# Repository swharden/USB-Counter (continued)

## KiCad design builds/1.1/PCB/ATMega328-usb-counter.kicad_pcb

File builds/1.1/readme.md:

# USB Frequency Counter (rev 1.1)

* I ordered this PCB on 2019-07-28
* I built this device on 2019-08-03

### PCB Design

### Schematic

## Changes from rev 1.0
* improved RF amplifier design
* alternate path to bypass RF amplifier
* corrected counter pin connections
* free a MCU pin by making the status LED the gate
* add a header for the serial LED display
* run MCU at 14.7456 MHz
  * allows much faster serial transmission
  * no longer accepts external 10MHz reference
  * may still accept external gate
* added screw holes
  * they're floating (not grounded) - should they be grounded?
* switched to micro USB (from mini USB)

## Components
* all passives are 0805 (~$1)
* [SBAV99WT1G SC-70 dual diode](https://www.mouser.com/ProductDetail/ON-Semiconductor/SBAV99WT1G?qs=%2Fha2pyFaduhs9dhfVWP8oT%252BsAj5t0ZSYddkb6PuTtd0%3D) 215 mA ($0.29)
* [14.7456MHz TCXO](https://www.mouser.com/ProductDetail/Fox/FOX924B-147456?qs=sGAEpiMZZMt8oz%2FHeiymADfzZKRiEXclvcmWd5jLzoM%3D) 2.5 PPM, 14.7456MHz ($2.36)
* [SN74LV8154](https://www.mouser.com/ProductDetail/Texas-Instruments/SN74LV8154PWR?qs=sGAEpiMZZMtdY2G%252BSI3N4aQvQNXOTGN6Ghdjz%252BkScFE%3D) ($0.99) TSSOP-20
* [FT230XS-R](https://www.mouser.com/ProductDetail/FTDI/FT230XS-R?qs=sGAEpiMZZMtv%252Bwxsgy%2FhiIaF6qCroMVR1i2pEQA5UpU%3D) ($2.04) SSOP-16
* [ATMega328](https://www.mouser.com/ProductDetail/Microchip-Technology-Atmel/ATMEGA328PB-AU?qs=sGAEpiMZZMvc81WFyF5EdrSRAEYMYvHlMc95YQj%2FArE%3D) ($1.38)
* [mini-USB jack](https://www.mouser.com/ProductDetail/CUI/UJ2-MBH-1-SMT-TR?qs=sGAEpiMZZMu3xu3GWjvQiLfiCTO8RP%252Bk%252BIiwpoT5qew%3D) ($0.49)
* [micro-USB jack](https://www.mouser.com/ProductDetail/Hirose-Connector/ZX62D-B-5PA830?qs=sGAEpiMZZMulM8LPOQ%252Byk6r3VmhUEyMLT8hu1C1GYL85FtczwhvFwQ%3D%3D) ($0.70)
* [SMA connector](https://www.mouser.com/ProductDetail/LPRS/SMA-CONNECTOR?qs=sGAEpiMZZMuLQf%252BEuFsOrkd7M7rmHNHidLMZ%2Ftb%252B0T1YCJLScw0qLA%3D%3D) ($1.08)
* [SPI-driven 8-digit 7-segment display module](https://www.amazon.com/dp/B07CL2YNJQ) ($13 for 4)

## Build Notes
* didnt have 27 ohm resistors. used 22 ohm.
* I used a 500mW rated R15
* I used a 500mW rated R13
* make hand solder version of usb
* make oscillator fit less awkwardly
* Add a 7805 so 12V can be applied or USB. Use a 78L33 (not the reg on the FTDI chip) to power everything else.
* This device doesn't work when plugged into a wall USB cord (power only, no data). It seems an active USB connection is required to cause the 3.3V regulator (built into the FTDI chip) to deliver power. The next revision should use a discrete 3.3V regulator.
* For a standalone (LED) device no USB connection is needed. Make a version that accepts 12V and displays the result on the LED. Make the optional external gate easy to access. Break-out the TX pin so PC logging is still very easy.

## Photos

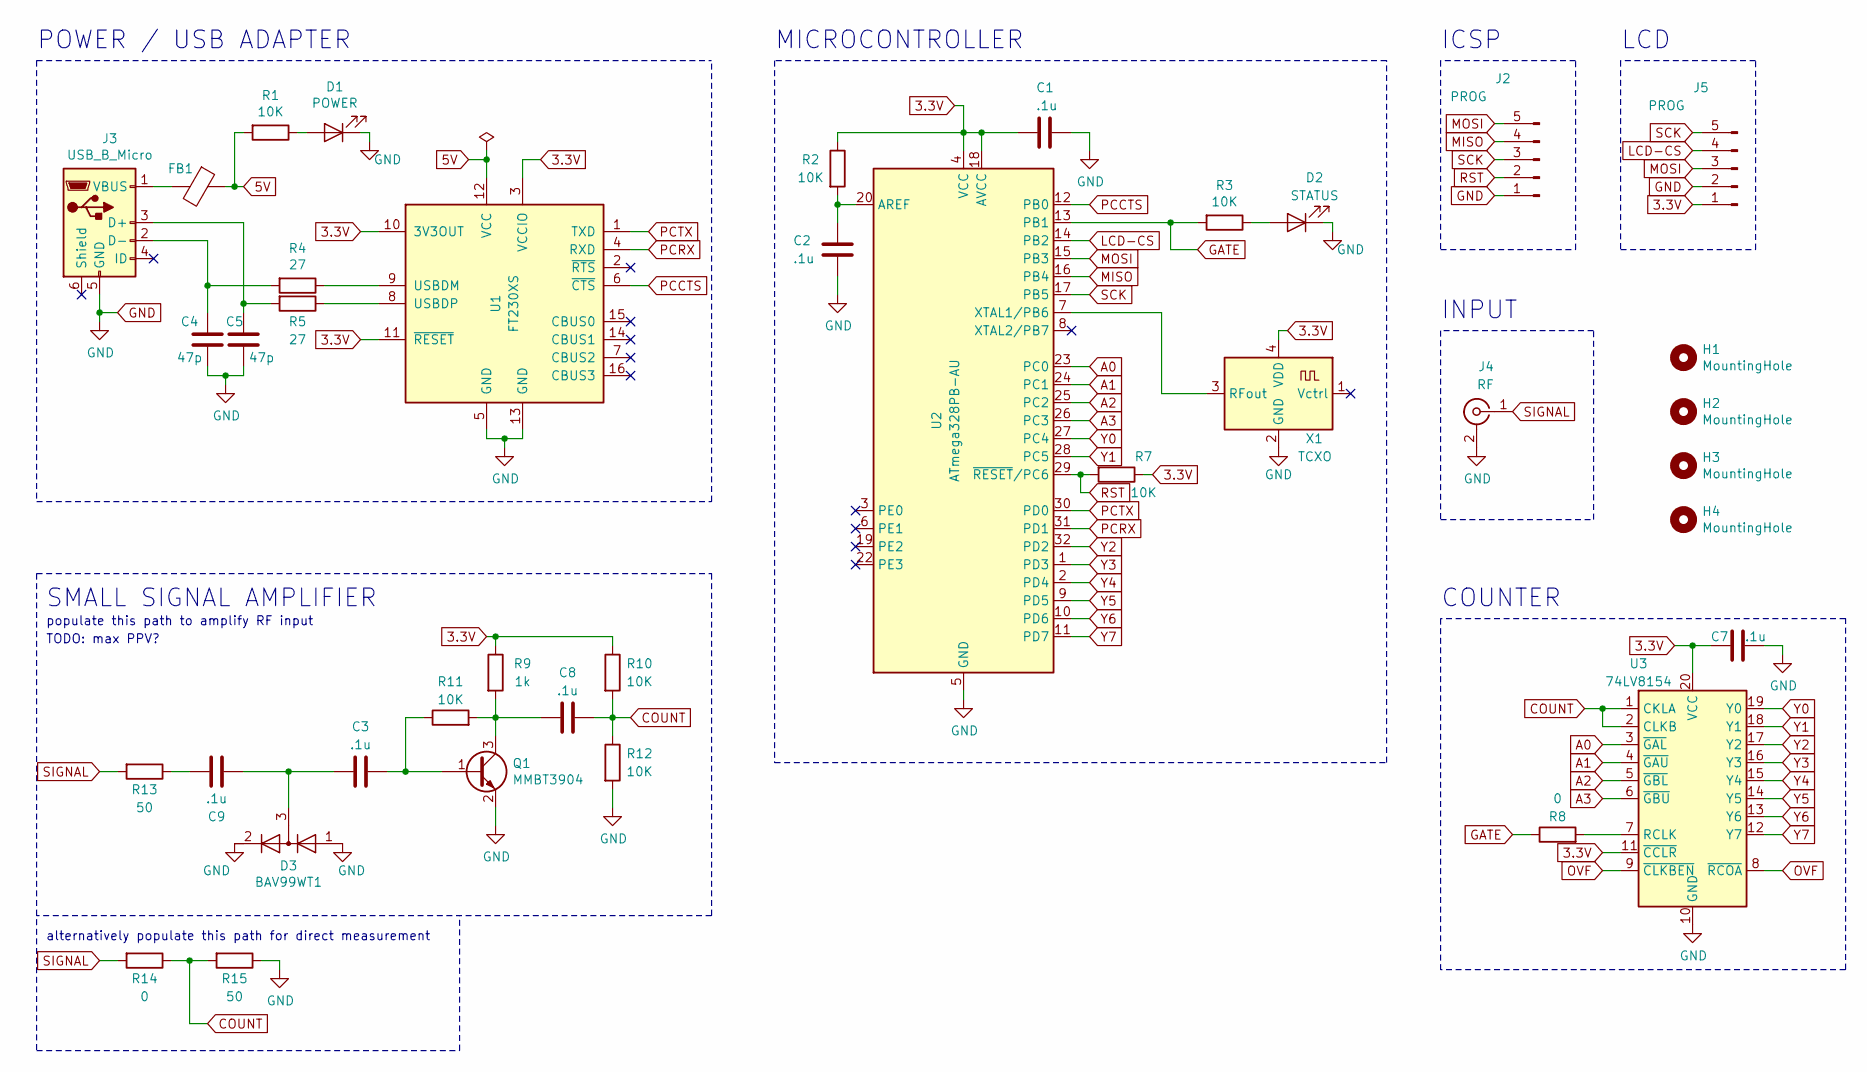
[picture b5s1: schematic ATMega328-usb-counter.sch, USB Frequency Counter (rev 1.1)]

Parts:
C1, C2, C3, C7, C8, C9: .1u; C_0805_2012Metric_Pad1.15x1.40mm_HandSolder
C4, C5: 47p; C_0805_2012Metric_Pad1.15x1.40mm_HandSolder
D1: POWER; LED_0805_2012Metric_Pad1.15x1.40mm_HandSolder
D2: STATUS; LED_0805_2012Metric_Pad1.15x1.40mm_HandSolder
D3: BAV99WT1; SOT-323_SC-70_Handsoldering
FB1: Ferrite; R_0805_2012Metric_Pad1.15x1.40mm_HandSolder
H1, H2, H3, H4: MountingHole; MountingHole_4.3mm_M4_Pad_Via
J2, J5: PROG; PinHeader_1x05_P2.54mm_Vertical
J3: USB_B_Micro; USB_Micro-B_Molex-105017-0001
J4: RF; SMA_Amphenol_901-144_Vertical
Q1: MMBT3904; SOT-23
R1, R2, R3, R7, R10, R11, R12: 10K; R_0805_2012Metric_Pad1.15x1.40mm_HandSolder
R4, R5: 27; R_0805_2012Metric_Pad1.15x1.40mm_HandSolder
R8, R14: 0; R_0805_2012Metric_Pad1.15x1.40mm_HandSolder
R9: 1k; R_0805_2012Metric_Pad1.15x1.40mm_HandSolder
R13, R15: 50; R_0805_2012Metric_Pad1.15x1.40mm_HandSolder
U1: FT230XS; SSOP-16_3.9x4.9mm_P0.635mm
U2: ATmega328PB-AU; TQFP-32_7x7mm_P0.8mm
U3: 74LV8154; TSSOP-20_4.4x6.5mm_P0.65mm
X1: TCXO; Oscillator_SMD_TXC_7C-4Pin_5.0x3.2mm_HandSoldering

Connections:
3.3V: C1.1, C7.1, J5.1, R2.1, R7.1, R9.1, R10.1, U1.3 (VCCIO), U1.10 (3V3OUT), U1.11 (~RESET), U2.4 (VCC), U2.18 (AVCC), U3.11 (~CCLR), U3.20 (VCC), X1.4 (VDD); also elsewhere on the board
5V: FB1.1, R1.2, U1.12 (VCC)
A0: U2.23 (PC0), U3.3 (~GAL)
A1: U2.24 (PC1), U3.4 (~GAU)
A2: U2.25 (PC2), U3.5 (~GBL)
A3: U2.26 (PC3), U3.6 (~GBU)
COUNT: C8.1, R10.2, R12.1, R14.1, R15.2, U3.1 (CKLA), U3.2 (CLKB)
GATE: R3.2, R8.1, U2.13 (PB1)
GND: C1.2, C2.1, C4.1, C5.1, C7.2, D1.1 (K), D2.1 (K), D3.1 (A), D3.2 (K), J2.1, J3.5 (GND), J4.2 (Ext), J5.2, Q1.2 (E), R12.2, R15.1, U1.5 (GND), U1.13 (GND), U2.5 (GND), U2.21 (GND), U3.10 (GND), X1.2 (GND); also elsewhere on the board
LCD-CS: J5.4, U2.14 (PB2)
MISO: J2.4, U2.16 (PB4)
MOSI: J2.5, J5.3, U2.15 (PB3)
unnamed: C2.2, R2.2, U2.20 (AREF)
unnamed: C3.1, Q1.1 (B), R11.1
unnamed: C3.2, C9.2, D3.3 (common)
unnamed: C4.2, J3.2 (D-), R4.2
unnamed: C5.2, J3.3 (D+), R5.2
unnamed: C8.2, Q1.3 (C), R9.2, R11.2
unnamed: C9.1, R13.1
unnamed: D1.2 (A), R1.1
unnamed: D2.2 (A), R3.1
unnamed: FB1.2, J3.1 (VBUS)
unnamed: R4.1, U1.9 (USBDM)
unnamed: R5.1, U1.8 (USBDP)
unnamed: R8.2, U3.7 (RCLK)
unnamed 26: U2.7 (XTAL1/PB6), X1.3 (RFout); also elsewhere on the board
OVF: U3.8 (~RCOA), U3.9 (~CLKBEN)
PCCTS: U1.6 (~CTS), U2.12 (PB0)
PCRX: U1.4 (RXD), U2.31 (PD1)
PCTX: U1.1 (TXD), U2.30 (PD0)
RST: J2.2, R7.2, U2.29 (~RESET~/PC6)
SCK: J2.3, J5.5, U2.17 (PB5)
SIGNAL: J4.1 (In), R13.2, R14.2
Y0: U2.27 (PC4), U3.19 (Y0)
Y1: U2.28 (PC5), U3.18 (Y1)
Y2: U2.32 (PD2), U3.17 (Y2)
Y3: U2.1 (PD3), U3.16 (Y3)
Y4: U2.2 (PD4), U3.15 (Y4)
Y5: U2.9 (PD5), U3.14 (Y5)
Y6: U2.10 (PD6), U3.13 (Y6)
Y7: U2.11 (PD7), U3.12 (Y7)

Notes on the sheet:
POWER / USB ADAPTER
MICROCONTROLLER
ICSP
SMALL SIGNAL AMPLIFIER
TODO: max PPV?
alternatively populate this path for direct measurement
populate this path to amplify RF input
COUNTER
INPUT
LCD

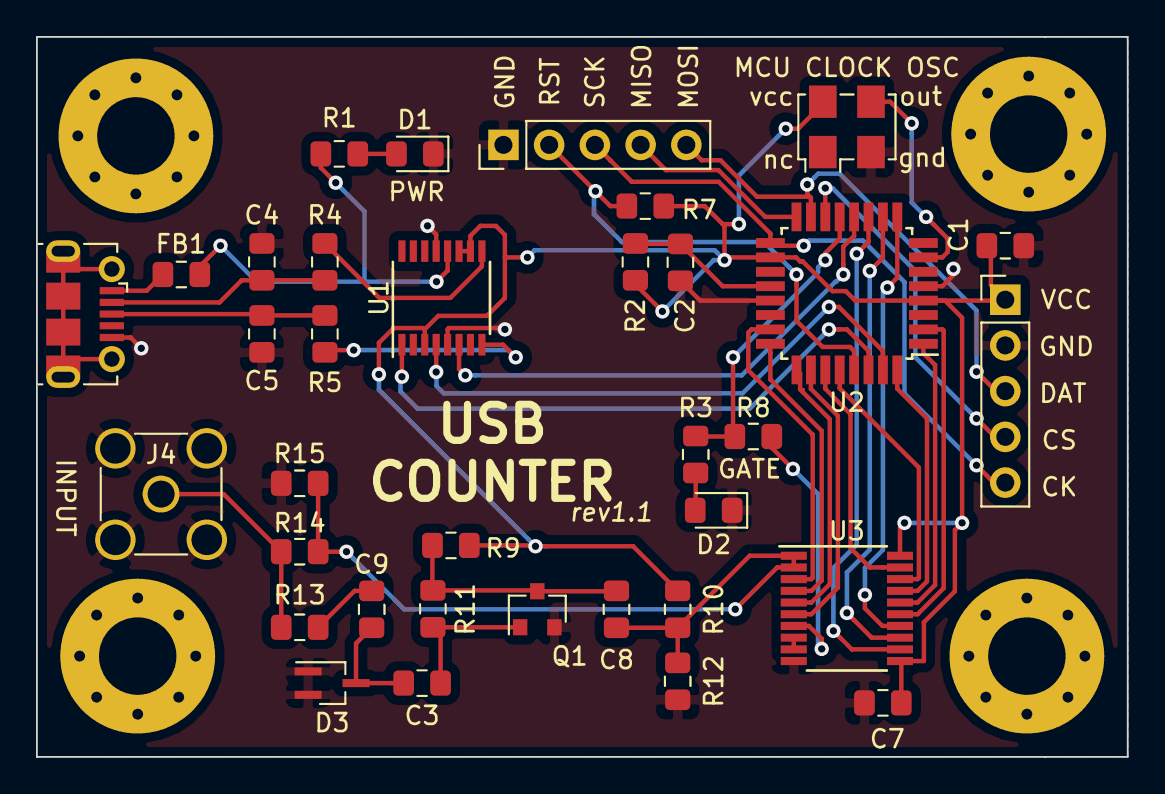
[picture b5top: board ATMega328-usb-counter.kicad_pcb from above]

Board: 2 copper layers, 60.6 x 40.0 mm, 39 parts (0 on the bottom side), 41 nets.

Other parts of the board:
MCU CLOCK OSC: TCXO; Oscillator_SMD_TXC_7C-4Pin_5.0x3.2mm_HandSoldering

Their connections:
3.3V: MCU CLOCK OSC.4; also elsewhere on the board
GND: MCU CLOCK OSC.2; also elsewhere on the board
unnamed 26: MCU CLOCK OSC.3; also elsewhere on the board

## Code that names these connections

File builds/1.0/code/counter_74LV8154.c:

/* code here is for interfacing the 74LV8154

 */

#include <avr/io.h>

char SetRegister(char registerNumber)
{
    DDRC |= 0b00001111; // set A0-A3 as outputs
    switch (registerNumber)
    {
    case (3):
        PORTC = 0b00000111; // A3
        break;
    case (2):
        PORTC = 0b00001011; // A2
        break;
    case (1):
        PORTC = 0b00001101; // A1
        break;
    case (0):
        PORTC = 0b00001110; // A0
        break;
    }
}

int ReadRegister(char registerNumber)
{
    SetRegister(registerNumber);

    // set inputs
    DDRC &= ~(1 << PC4);
    DDRC &= ~(1 << PC5);

    DDRD &= ~(1 << PD2);
    DDRD &= ~(1 << PD3);
    DDRD &= ~(1 << PD4);
    DDRD &= ~(1 << PD5);
    DDRD &= ~(1 << PD6);
    DDRD &= ~(1 << PD7);

    int value = 0;

    if ((PINC & (1 << PC4)))
        value |= 0b00000001;

    if ((PINC & (1 << PC5)))
        value |= 0b00000010;

    if ((PIND & (1 << PD2)))
        value |= 0b00000100;

    if ((PIND & (1 << PD3)))
        value |= 0b00001000;

    if ((PIND & (1 << PD4)))
        value |= 0b00010000;

    if ((PIND & (1 << PD5)))
        value |= 0b00100000;

    if ((PIND & (1 << PD6)))
        value |= 0b01000000;

    if ((PIND & (1 << PD7)))
        value |= 0b10000000;

    return value;
}

uint32_t ReadCount()
{
    uint32_t value = 0;

    value += ReadRegister(3);
    value = value << 8;

    value += ReadRegister(2);
    value = value << 8;

    value += ReadRegister(1);
    value = value << 8;

    value += ReadRegister(0);

    return value;

    //SerialSendLongASCII(value);
    //SerialSendBreak();
}

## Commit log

2019-07-26 initial upload
2019-07-26 fixed counter bug
2019-07-26 rev 1.1 works
2019-07-27 improve front-end
2019-07-28 update simulation
2019-07-28 rev 1.2 schematic
2019-07-28 rev 1.1 PCB
2019-07-28 added screw hole
2019-07-28 improve silkscreen
2019-07-28 cap sensitivity
2019-07-28 new diode protection
2019-07-28 move usb connector to board edge
2019-08-02 tested 100Hz update rate
2019-08-02 100Hz tested better
2019-08-03 add build 1.1 photos
2019-08-03 improve photos
2019-08-04 counter works
    fixed huge glitch caused by PB2 != PB1
2019-08-04 7-segment display works
2019-08-04 works well for 1hz
2019-08-04 pull spi lines high
2019-08-04 update photos
2019-08-04 3.3V regulator note
2019-08-04 sigGen
2019-08-07 100hz pulse counter documentation
2022-11-19 counter 2.0
2022-11-19 USB Counter 2.0: add 3.3v regulator
2022-11-19 2.0: improve wiring
2022-11-20 3.0: improve annotations
2022-11-20 3.0: assign footprints
2022-11-20 2.0: ready to fabricate
2022-11-22 3.0: update frontend
2022-11-23 2.0: input protection and amplification
2022-11-23 2.0: update footprints
2022-11-23 2.0: reset PCB
    using JLCPCB rules
2022-11-23 3.0: update netlist
2022-11-23 3.0: new board
2022-11-27 2.0: improve layout
2022-11-27 move 2.0 -> 2.1
2022-11-28 2.1: gerbers
2022-11-28 2.1: update PCB file after gerber export
2022-12-10 v2.2: start project
2022-12-11 2.2: USB interface schematic
2022-12-11 2.2: input signal shaper
2022-12-12 2.2: comparator frontend
2022-12-13 2.2: update notes
2022-12-14 2.2: update schematic
2022-12-14 2.2: update footprints
2022-12-14 2.2: netlist
2022-12-14 2.2 PCB: rough layout and design rules
2022-12-14 2.2 PCB: complete
2022-12-15 2.2: gerbers
2022-12-23 AVRDD64: oscillator and serial
2023-09-03 start talking counter project
2023-09-03 frontend amplifier
2023-09-04 update schematic
2023-09-06 fix erc issues
2023-09-06 update footprints
2023-09-06 custom speaker symbol
2023-09-06 first pass layout
2023-09-06 layout pcb
2023-09-06 PCB updates based on DRC
2023-09-12 build 2.3 test software
2023-09-12 3.2: delete software
2023-09-12 copy software from talking counter
2023-09-12 update firmware
2023-09-13 2.3: improve software
2023-09-16 usbc connector
2023-10-01 create PCB
2023-10-01 update pcb
2023-10-01 move labels
2023-10-12 3.0 software
2023-10-12 use original button wiring
2023-10-21 improve software
